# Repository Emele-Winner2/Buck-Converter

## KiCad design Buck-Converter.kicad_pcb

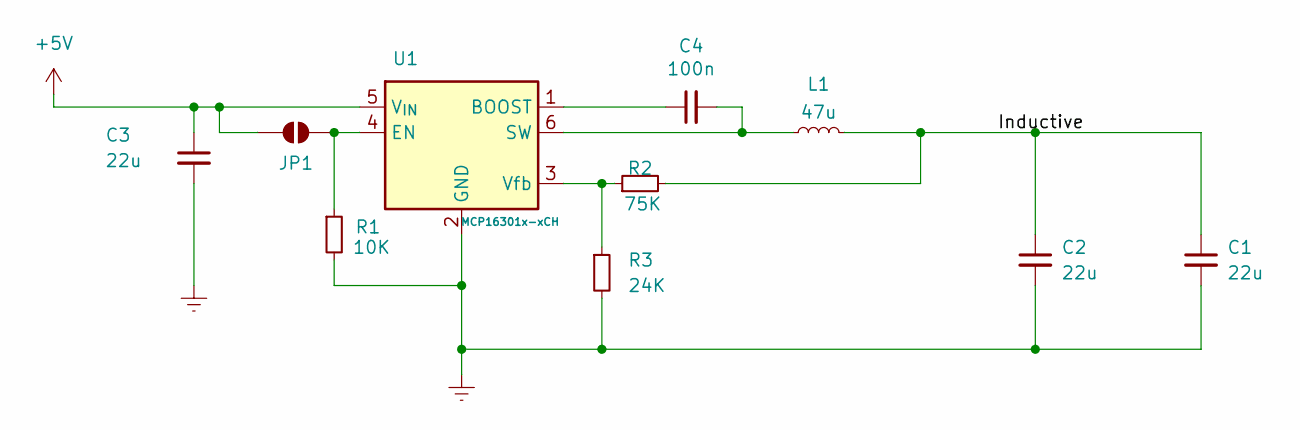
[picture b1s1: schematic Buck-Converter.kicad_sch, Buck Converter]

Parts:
C1, C2, C3: 22u; C_0603_1608Metric_Pad1.08x0.95mm_HandSolder
C4: 100n; C_0603_1608Metric_Pad1.08x0.95mm_HandSolder
JP1: SolderJumper_2_Open; SolderJumper-2_P1.3mm_Open_Pad1.0x1.5mm
L1: 47u; L_0603_1608Metric_Pad1.05x0.95mm_HandSolder
R1: 10K; R_0603_1608Metric_Pad0.98x0.95mm_HandSolder
R2: 75K; R_0603_1608Metric_Pad0.98x0.95mm_HandSolder
R3: 24K; R_0603_1608Metric_Pad0.98x0.95mm_HandSolder
U1: MCP16301x-xCH; SOT-23-6

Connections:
+5V: C3.1, JP1.1 (A), U1.5 (V_{IN})
/Inductive: C1.1, C2.1, L1.2, R2.2
Earth: C1.2, C2.2, C3.2, R1.2, R3.2, U1.2 (GND)
unnamed: JP1.2 (B), R1.1, U1.4 (EN)
unnamed: C4.1, U1.1 (BOOST)
unnamed: C4.2, L1.1, U1.6 (SW)
unnamed: R2.1, R3.1, U1.3 (Vfb)

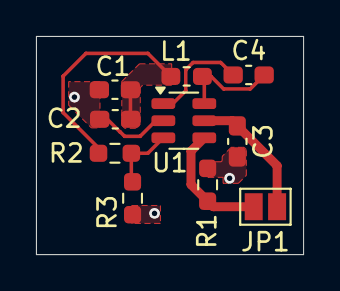
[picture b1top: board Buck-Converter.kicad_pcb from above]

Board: 2 copper layers, 14.8 x 12.1 mm, 10 parts (0 on the bottom side), 7 nets.
